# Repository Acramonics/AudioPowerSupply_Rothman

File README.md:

AudioPowerSupply
================

Board Design: Andrew Martin, Acramonics, 2026

Circuit Design: Jake Rothmann

Overview
--------

This is a redesign of the PCB for Jake Rothmann's dual-rail power
supply for high quality audio work. The original board is rather large
and this version has been shrunk for use in my builds.

Note that the board suppors 15V-0-15V, 21V-0-21V, or 48V single rail.

The 21V-0-21V is designed as the best supply for NE5532s, but the
newer versions of these only support up to 18V-0-18V rails.

The 48V single rail is designed for microphone phantom power.

The component values in the schematic are for the 21V-0-21V version
(except where components are not present in that version, where they
are for the 15V-0-15V version). **Make sure to read the schematic
together with the BOM**

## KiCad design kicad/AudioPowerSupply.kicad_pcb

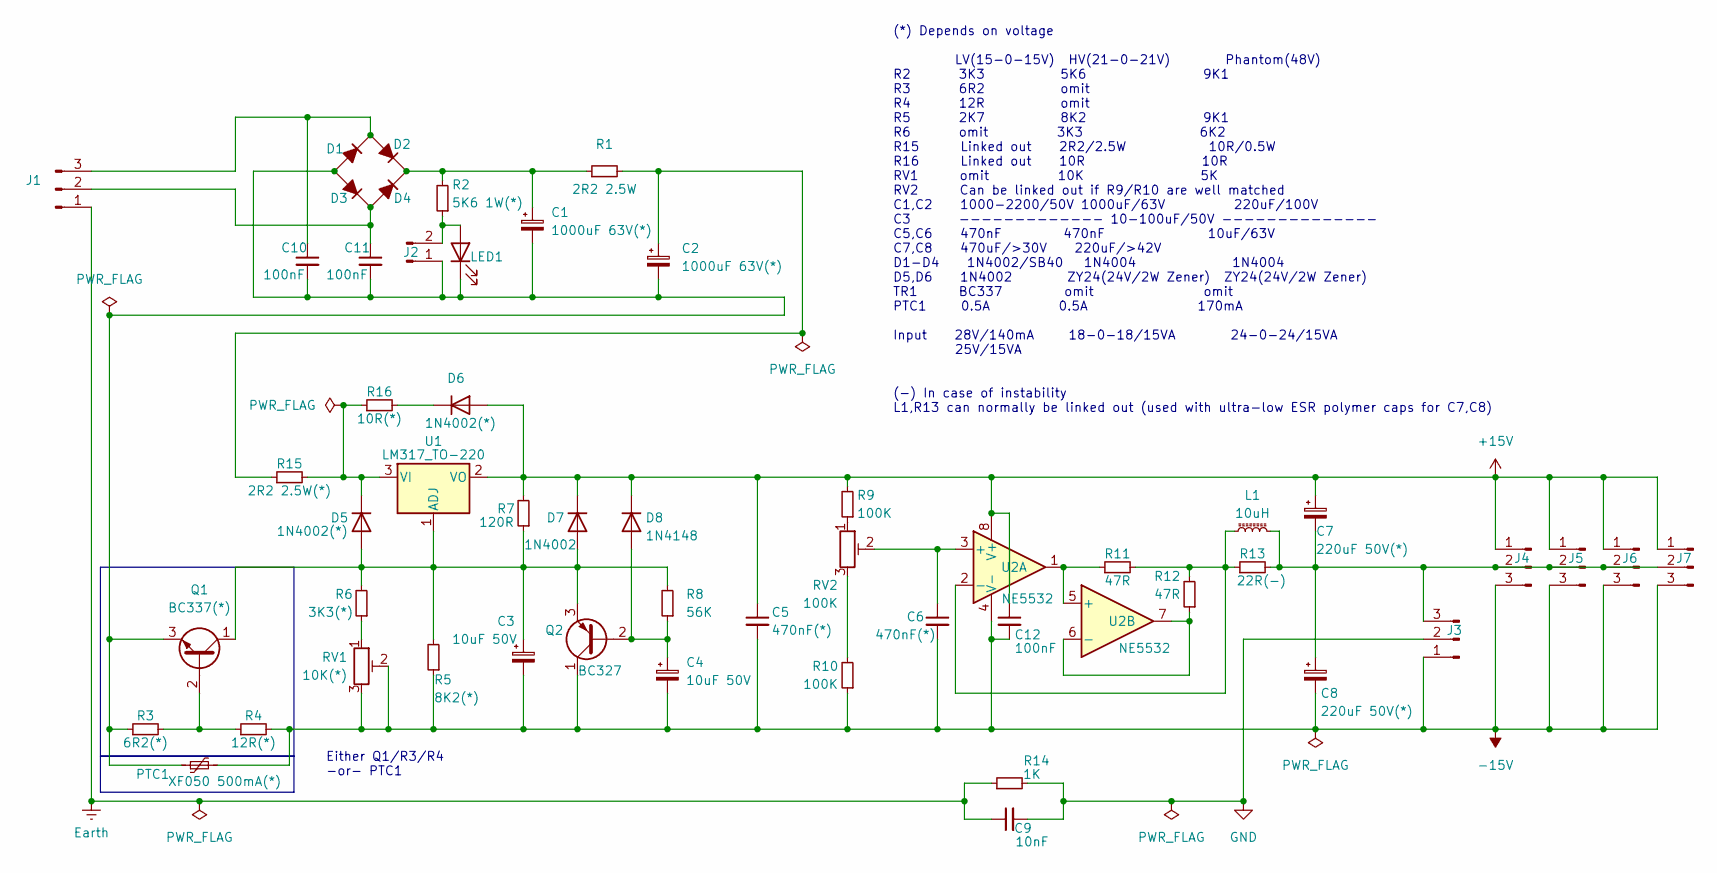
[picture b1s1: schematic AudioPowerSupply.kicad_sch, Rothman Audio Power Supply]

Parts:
C1, C2: 1000uF 63V(*); CP_Radial_D16.0mm_P7.50mm
C3, C4: 10uF 50V; CP_Radial_D5.0mm_P2.50mm
C5, C6: 470nF(*); C_Rect_L7.2mm_W3.0mm_P5.00mm_FKS2_FKP2_MKS2_MKP2
C7, C8: 220uF 50V(*); CP_Radial_D10.0mm_P5.00mm
C9: 10nF; C_Rect_L7.2mm_W3.0mm_P5.00mm_FKS2_FKP2_MKS2_MKP2
C10, C11, C12: 100nF; C_Rect_L7.2mm_W3.0mm_P5.00mm_FKS2_FKP2_MKS2_MKP2
D1, D2, D3, D4: 1N4001; D_DO-41_SOD81_P10.16mm_Horizontal
D5, D6: 1N4002(*); D_DO-41_SOD81_P10.16mm_Horizontal
D7: 1N4002; D_DO-41_SOD81_P10.16mm_Horizontal
D8: 1N4148; D_DO-35_SOD27_P7.62mm_Horizontal
J1, J4, J5, J6, J7: Conn_01x03_Pin; TerminalBlock_4Ucon_1x03_P3.50mm_Vertical
J2: Conn_01x02_Pin; Molex_KK-254_AE-6410-02A_1x02_P2.54mm_Vertical
J3: Conn_01x03_Pin; PinHeader_1x03_P2.54mm_Vertical
L1: 10uH; L_Axial_L9.5mm_D4.0mm_P12.70mm_Horizontal_Fastron_SMCC
LED1: LED
PTC1: XF050 500mA(*); RV_Disc_D9mm_W3.3mm_P5mm
Q1: BC337(*); TO-92_Inline
Q2: BC327; TO-92_Inline
R1: 2R2 2.5W; R_Axial_DIN0414_L11.9mm_D4.5mm_P15.24mm_Horizontal
R2: 5K6 1W(*); R_Axial_DIN0414_L11.9mm_D4.5mm_P15.24mm_Horizontal
R3: 6R2(*); R_Axial_DIN0207_L6.3mm_D2.5mm_P10.16mm_Horizontal
R4: 12R(*); R_Axial_DIN0207_L6.3mm_D2.5mm_P10.16mm_Horizontal
R5: 8K2(*); R_Axial_DIN0207_L6.3mm_D2.5mm_P10.16mm_Horizontal
R6: 3K3(*); R_Axial_DIN0207_L6.3mm_D2.5mm_P10.16mm_Horizontal
R7: 120R; R_Axial_DIN0207_L6.3mm_D2.5mm_P10.16mm_Horizontal
R8: 56K; R_Axial_DIN0207_L6.3mm_D2.5mm_P10.16mm_Horizontal
R9, R10: 100K; R_Axial_DIN0207_L6.3mm_D2.5mm_P10.16mm_Horizontal
R11, R12: 47R; R_Axial_DIN0207_L6.3mm_D2.5mm_P10.16mm_Horizontal
R13: 22R(-); R_Axial_DIN0207_L6.3mm_D2.5mm_P10.16mm_Horizontal
R14: 1K; R_Axial_DIN0207_L6.3mm_D2.5mm_P2.54mm_Vertical
R15: 2R2 2.5W(*); R_Axial_DIN0414_L11.9mm_D4.5mm_P15.24mm_Horizontal
R16: 10R(*); R_Axial_DIN0207_L6.3mm_D2.5mm_P10.16mm_Horizontal
RV1: 10K(*); Potentiometer_Piher_PT-10-V05_Vertical
RV2: 100K; Potentiometer_Piher_PT-10-V05_Vertical
U1: LM317_TO-220; TO-220-3_Vertical
U2: NE5532; DIP-8_W7.62mm

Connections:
+15V: C5.1, C7.1, C12.1, D6.2 (A), D7.1 (K), D8.1 (K), J4.1, J5.1, J6.1, J7.1, R7.2, R9.2, U1.2 (VO), U2.8 (V+)
-15V: C3.2, C4.2, C5.2, C6.2, C8.2, C12.2, J3.1, J4.3, J5.3, J6.3, J7.3, PTC1.2, Q2.1 (C), R4.2, R5.1, R10.1, RV1.2, RV1.3, U2.4 (V-)
Earth: C9.1, J1.1, R14.1
GND: C9.2, J3.2, R14.2
unnamed: C2.1, R1.2, R15.1
unnamed: C1.2, C2.2, C10.2, C11.2, D1.2 (A), D3.2 (A), J2.1, LED1.1 (K), PTC1.1, Q1.3 (E), R3.1
unnamed: C10.1, D1.1 (K), D2.2 (A), J1.3
unnamed: C1.1, D2.1 (K), D4.1 (K), R1.1, R2.2
unnamed: C11.1, D3.1 (K), D4.2 (A), J1.2
unnamed: C3.1, D5.2 (A), D7.2 (A), Q1.1 (C), Q2.3 (E), R5.2, R6.2, R7.1, R8.2, U1.1 (ADJ)
unnamed: D5.1 (K), R15.2, R16.1, U1.3 (VI)
unnamed: D6.1 (K), R16.2
unnamed: C4.1, D8.2 (A), Q2.2 (B), R8.1
unnamed: J2.2, LED1.2 (A), R2.1
unnamed: C7.2, C8.1, J3.3, J4.2, J5.2, J6.2, J7.2, L1.2, R13.2
unnamed: Q1.2 (B), R3.2, R4.1
unnamed: R6.1, RV1.1
unnamed: R9.1, RV2.1
unnamed: R10.2, RV2.3
unnamed: C6.1, RV2.2, U2.3 (+)
unnamed: L1.1, R11.2, R12.2, R13.1, U2.2 (-)
unnamed: R11.1, U2.1, U2.5 (+)
unnamed: R12.1, U2.6 (-), U2.7

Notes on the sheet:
Either Q1/R3/R4 -or- PTC1
(*) Depends on voltage LV(15-0-15V) HV(21-0-21V) Phantom(48V) R2 3K3 5K6 9K1 R3 6R2 omit R4 12R omit R5 2K7 8K2 9K1 R6 omit 3K3 6K2 R15 Linked out 2R2/2.5W 10R/0.5W R16 Linked out 10R 10R RV1 omit 10K 5K RV2 Can be linked out if R9/R10 are well matched C1,C2 1000-2200/50V 1000uF/63V 220uF/100V C3 -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

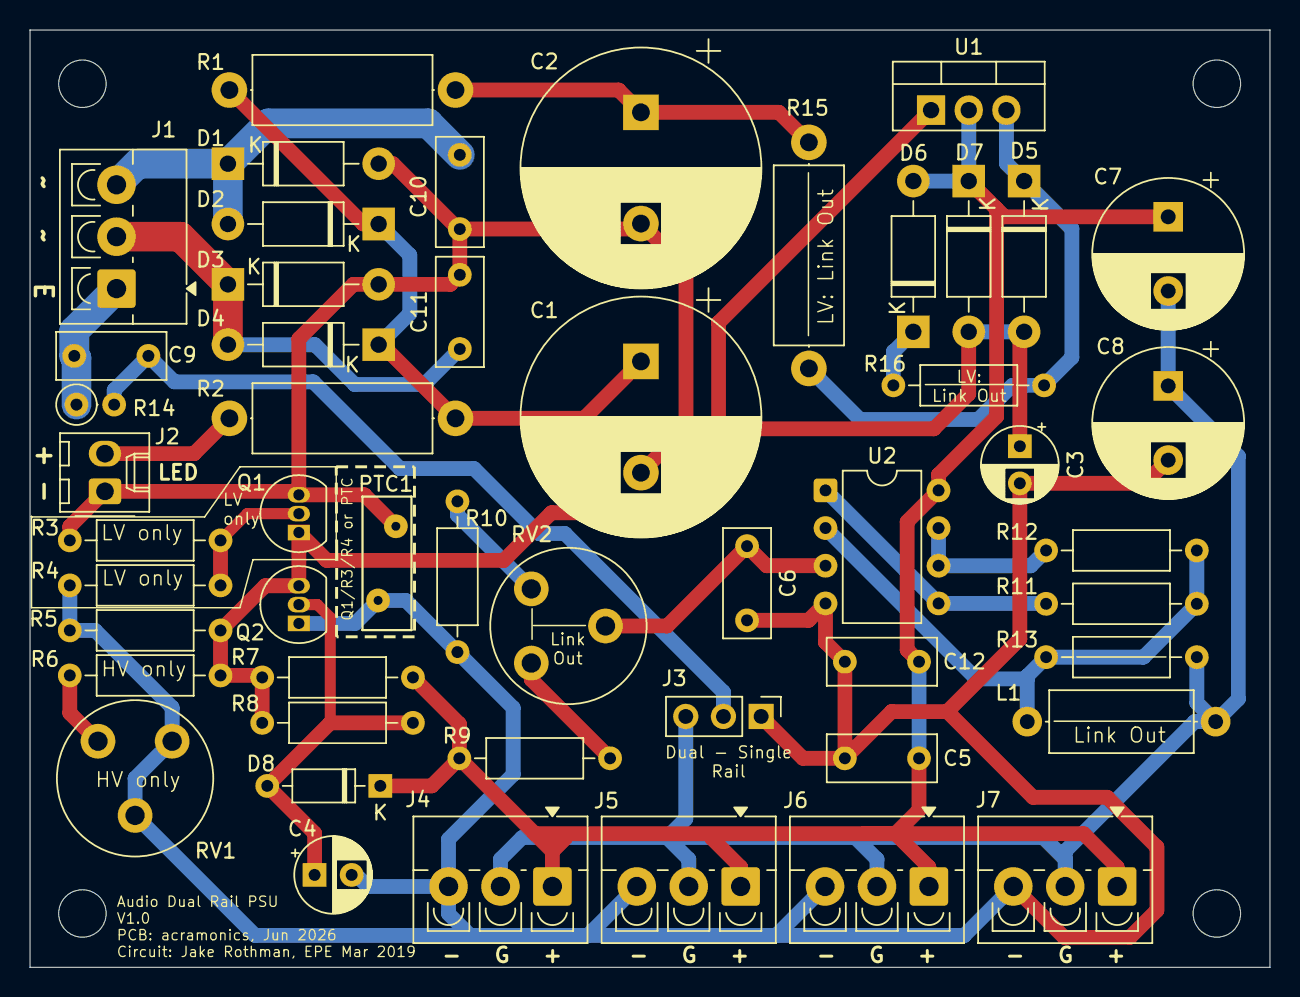
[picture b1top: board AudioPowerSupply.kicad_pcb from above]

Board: 2 copper layers, 83.6 x 63.2 mm, 51 parts (0 on the bottom side), 23 nets.

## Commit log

2026-06-09 Complete V1.0
2026-06-09 Renamed gerber zip
2026-06-09 Corrected Readme
